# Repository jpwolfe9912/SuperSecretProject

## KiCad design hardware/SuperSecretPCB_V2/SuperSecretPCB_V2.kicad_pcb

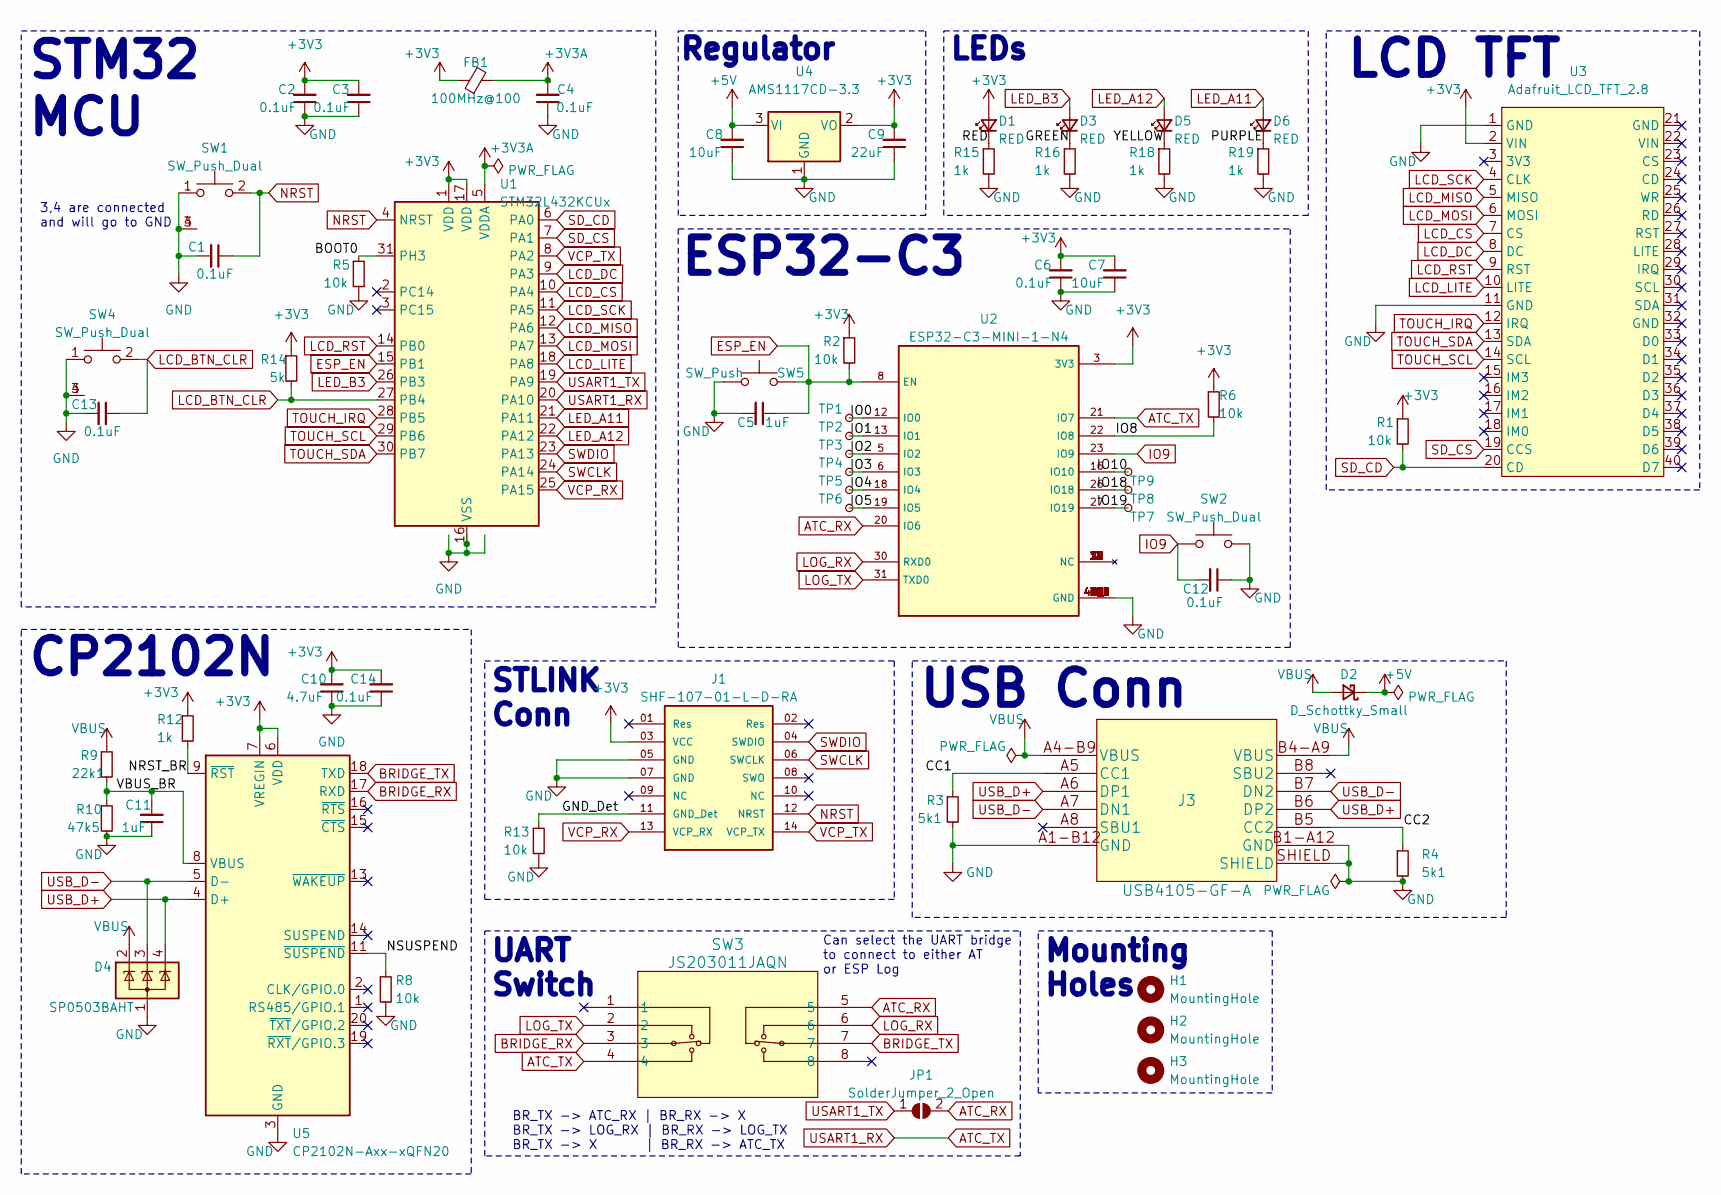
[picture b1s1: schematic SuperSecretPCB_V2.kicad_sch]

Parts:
C1, C2, C3, C4, C6, C12, C13, C14: 0.1uF; C_0603_1608Metric
C5, C11: 1uF; C_0603_1608Metric
C7, C8: 10uF; C_0603_1608Metric
C9: 22uF; C_0603_1608Metric
C10: 4.7uF; C_0603_1608Metric
D1, D3, D5, D6: RED; LED_D5.0mm_Horizontal_O1.27mm_Z3.0mm
D2: D_Schottky_Small; D_0603_1608Metric
D4: SP0503BAHT; SOT-143
FB1: 100MHz@100; C_0603_1608Metric
H1, H2, H3: MountingHole; MountingHole_2.2mm_M2
J1: SHF-107-01-L-D-RA; SAMTEC_SHF-107-01-L-D-RA
J3: USB4105-GF-A; GCT_USB4105-GF-A
JP1: SolderJumper_2_Open; PinHeader_1x02_P2.54mm_Vertical
R1, R2, R5, R6, R8, R13: 10k; R_0603_1608Metric
R3, R4: 5k1; R_0603_1608Metric
R9: 22k1; R_0603_1608Metric
R10: 47k5; R_0603_1608Metric
R12, R15, R16, R18, R19: 1k; R_0603_1608Metric
R14: 5k; R_0603_1608Metric
SW1, SW4: SW_Push_Dual; Switch_1825027-5
SW2: SW_Push_Dual; SW_SPST_B3U-1000P
SW3: JS203011JAQN; SW8_JS203011JAQN_CNK
SW5: SW_Push; SW_SPST_B3U-1000P
TP1, TP2, TP3, TP4, TP5, TP6, TP7, TP8, TP9: TP; TestPoint_Pad_D1.0mm
U1: STM32L432KCUx; QFN-32-1EP_5x5mm_P0.5mm_EP3.45x3.45mm
U2: ESP32-C3-MINI-1-N4; XCVR_ESP32-C3-MINI-1-N4; PARTREV v1.0
U3: Adafruit_LCD_TFT_2.8
U4: AMS1117CD-3.3; TO-252-2
U5: CP2102N-Axx-xQFN20; SiliconLabs_QFN-20-1EP_3x3mm_P0.5mm_EP1.8x1.8mm

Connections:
+3V3: C2.2, C3.2, C6.2, C7.2, C9.2, C10.2, C14.2, D1.2 (A), FB1.1, J1.03 (VCC), R1.1, R2.1, R6.1, R12.1, R14.1, U1.1 (VDD), U1.17 (VDD), U2.3 (3V3), U3.2 (VIN), U4.2 (VO), U5.6 (VDD), U5.7 (VREGIN)
+3V3A: C4.2, FB1.2, U1.5 (VDDA)
+5V: C8.2, D2.1 (K), U4.3 (VI)
/BOOT0: R5.1, U1.31 (PH3)
/CC1: J3.A5 (CC1), R3.1
/CC2: J3.B5 (CC2), R4.1
/GND_Det: J1.11 (GND_Det), R13.1
/GREEN: D3.1 (K), R16.1
/IO0: TP1.1, U2.12 (IO0)
/IO1: TP2.1, U2.13 (IO1)
/IO2: TP3.1, U2.5 (IO2)
/IO3: TP4.1, U2.6 (IO3)
/IO4: TP5.1, U2.18 (IO4)
/IO5: TP6.1, U2.19 (IO5)
/IO8: R6.2, U2.22 (IO8)
/IO10: TP9.1, U2.16 (IO10)
/IO18: TP8.1, U2.26 (IO18)
/IO19: TP7.1, U2.27 (IO19)
/NRST_BR: R12.2, U5.9 (~RST)
/NSUSPEND: R8.1, U5.11 (~SUSPEND)
/PURPLE: D6.1 (K), R19.1
/RED: D1.1 (K), R15.1
/VBUS_BR: C11.2, R9.2, R10.1, U5.8 (VBUS)
/YELLOW: D5.1 (K), R18.1
ATC_RX: JP1.2 (B), SW3.5, U2.20 (IO6)
ATC_TX: SW3.4, U1.20 (PA10), U2.21 (IO7)
BRIDGE_RX: SW3.3, U5.17 (RXD)
BRIDGE_TX: SW3.7, U5.18 (TXD)
ESP_EN: C5.1, R2.2, SW5.2, U1.15 (PB1), U2.8 (EN)
GND: C1.2, C2.1, C3.1, C4.1, C5.2, C6.1, C7.1, C8.1, C9.1, C10.1, C11.1, C12.1, C13.2, C14.1, D4.1 (A), J1.05 (GND), J1.07 (GND), J3.A1-B12 (GND), J3.B1-A12 (GND), J3.SHIELD, R3.2, R4.2, R5.2, R8.2, R10.2, R13.2, R15.2, R16.2, R18.2, R19.2, SW1.1, SW1.3, SW1.4, SW2.2, SW4.1, SW4.3, SW4.4, SW5.1, U1.16 (VSS), U1.32 (VSS), U1.33 (VSS), U2.1 (GND), U2.2 (GND), U2.11 (GND), U2.14 (GND), U2.36 (GND), U2.37 (GND), U2.38 (GND), U2.39 (GND), U2.40 (GND), U2.41 (GND), U2.42 (GND), U2.43 (GND), U2.44 (GND), U2.45 (GND), U2.46 (GND), U2.47 (GND), U2.48 (GND), U2.49_1 (GND), U2.49_2 (GND), U2.49_3 (GND), U2.49_4 (GND), U2.49_5 (GND), U2.49_6 (GND), U2.49_7 (GND), U2.49_8 (GND), U2.49_9 (GND), U2.50 (GND), U2.51 (GND), U2.52 (GND), U2.53 (GND), U3.1 (GND), U3.11 (GND), U4.1 (GND), U5.3 (GND), U5.12 (GND), U5.21 (GND)
IO9: C12.2, SW2.1, U2.23 (IO9)
LCD_BTN_CLR: C13.1, R14.2, SW4.2, U1.27 (PB4)
LCD_CS: U1.10 (PA4), U3.7 (CS)
LCD_DC: U1.9 (PA3), U3.8 (DC)
LCD_LITE: U1.18 (PA8), U3.10 (LITE)
LCD_MISO: U1.12 (PA6), U3.5 (MISO)
LCD_MOSI: U1.13 (PA7), U3.6 (MOSI)
LCD_RST: U1.14 (PB0), U3.9 (RST)
LCD_SCK: U1.11 (PA5), U3.4 (CLK)
LED_A11: D6.2 (A), U1.21 (PA11)
LED_A12: D5.2 (A), U1.22 (PA12)
LED_B3: D3.2 (A), U1.26 (PB3)
LOG_RX: SW3.6, U2.30 (RXD0)
LOG_TX: SW3.2, U2.31 (TXD0)
NRST: C1.1, J1.12 (NRST), SW1.2, U1.4 (NRST)
SD_CD: R1.2, U1.6 (PA0), U3.20 (CD)
SD_CS: U1.7 (PA1), U3.19 (CCS)
SWCLK: J1.06 (SWCLK), U1.24 (PA14)
SWDIO: J1.04 (SWDIO), U1.23 (PA13)
TOUCH_IRQ: U1.28 (PB5), U3.12 (IRQ)
TOUCH_SCL: U1.29 (PB6), U3.14 (SCL)
TOUCH_SDA: U1.30 (PB7), U3.13 (SDA)
USART1_TX: JP1.1 (A), U1.19 (PA9)
USB_D+: D4.4 (K), J3.A6 (DP1), J3.B6 (DP2), U5.4 (D+)
USB_D-: D4.3 (K), J3.A7 (DN1), J3.B7 (DN2), U5.5 (D-)
VBUS: D2.2 (A), D4.2 (K), J3.A4-B9 (VBUS), J3.B4-A9 (VBUS), R9.1
VCP_RX: J1.13 (VCP_RX), U1.25 (PA15)
VCP_TX: J1.14 (VCP_TX), U1.8 (PA2)

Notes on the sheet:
STLINK Conn
LEDs
UART Switch
STM32 MCU
BR_TX -> ATC_RX | BR_RX -> X BR_TX -> LOG_RX | BR_RX -> LOG_TX BR_TX -> X | BR_RX -> ATC_TX
CP2102N
Regulator
ESP32-C3
LCD TFT
Can select the UART bridge to connect to either AT or ESP Log
Mounting Holes
USB Conn
3,4 are connected and will go to GND

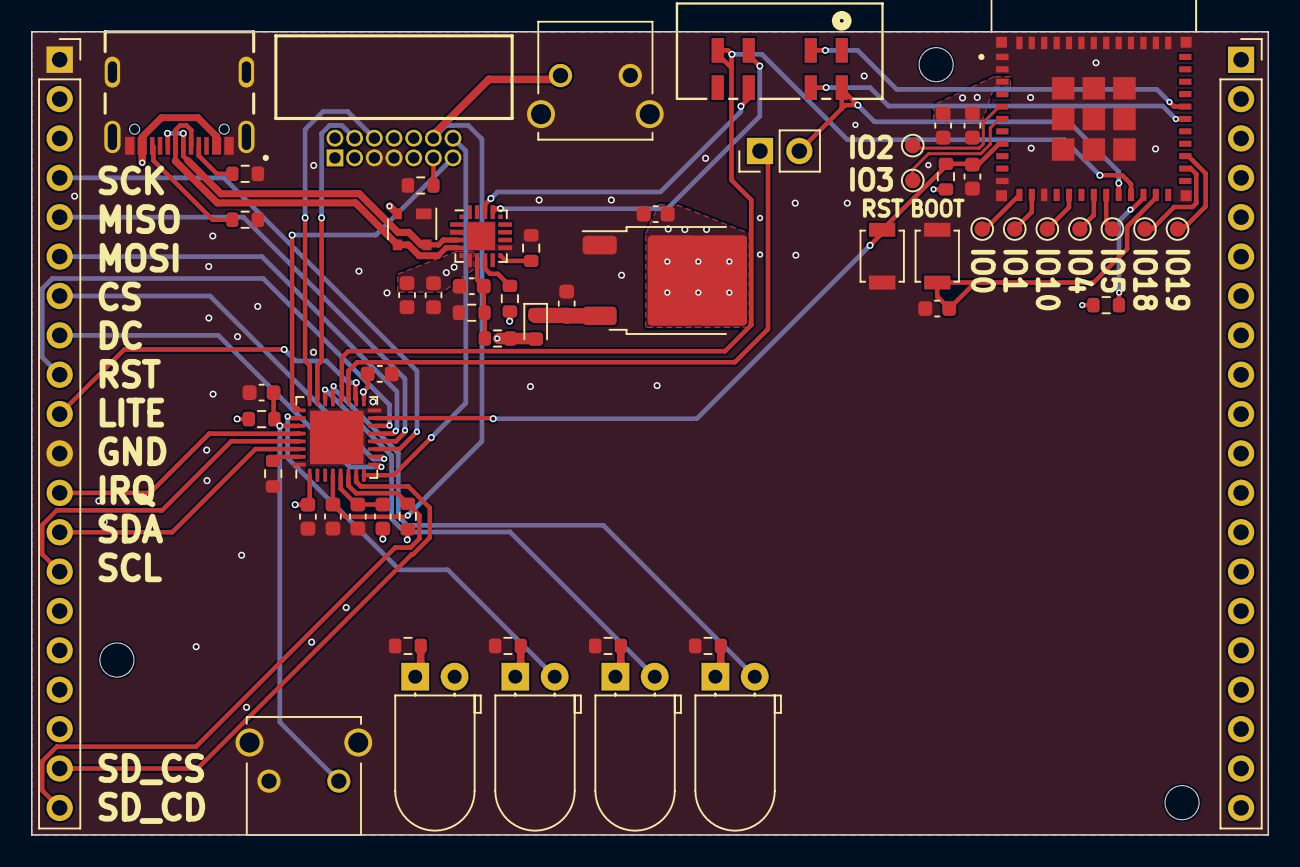
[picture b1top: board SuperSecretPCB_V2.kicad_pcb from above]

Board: 4 copper layers, 79.8 x 51.8 mm, 62 parts (0 on the bottom side), 58 nets.

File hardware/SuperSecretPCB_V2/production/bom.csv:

Designator,Footprint,Quantity,Value,LCSC Part #
"C1, C12, C13, C14, C2, C3, C4, C6",0603,8,0.1uF,
C10,0603,1,4.7uF,
"C11, C5",0603,2,1uF,
"C7, C8",0603,2,10uF,
C9,0603,1,22uF,
"D1, D3, D5, D6",LED_D5.0mm_Horizontal_O1.27mm_Z3.0mm,4,RED,
D2,0603,1,D_Schottky_Small,
D4,SOT-143,1,SP0503BAHT,
FB1,0603,1,100MHz@100,
"H1, H2, H3",MountingHole_2.2mm_M2,3,MountingHole,
J1,SAMTEC_SHF-107-01-L-D-RA,1,SHF-107-01-L-D-RA,
J3,GCT_USB4105-GF-A,1,USB4105-GF-A,
JP1,PinHeader_1x02_P2.54mm_Vertical,1,SolderJumper_2_Open,
"R1, R13, R2, R5, R6, R8",0603,6,10k,
R10,0603,1,47k5,
"R12, R15, R16, R18, R19",0603,5,1k,
R14,0603,1,5k,
"R3, R4",0603,2,5k1,
R9,0603,1,22k1,
"SW1, SW4",Switch_1825027-5,2,SW_Push_Dual,
SW2,SW_SPST_B3U-1000P,1,SW_Push_Dual,
SW3,SW8_JS203011JAQN_CNK,1,JS203011JAQN,
SW5,SW_SPST_B3U-1000P,1,SW_Push,
"TP1, TP2, TP3, TP4, TP5, TP6, TP7, TP8, TP9",TestPoint_Pad_D1.0mm,9,TP,
U1,QFN-32-1EP_5x5mm_P0.5mm_EP3.45x3.45mm,1,STM32L432KCUx,
U2,XCVR_ESP32-C3-MINI-1-N4,1,ESP32-C3-MINI-1-N4,
U3,Adafruit_LCD_TFT_2.8,1,Adafruit_LCD_TFT_2.8,
U4,TO-252-2,1,AMS1117CD-3.3,
U5,SiliconLabs_QFN-20-1EP_3x3mm_P0.5mm_EP1.8x1.8mm,1,CP2102N-Axx-xQFN20,

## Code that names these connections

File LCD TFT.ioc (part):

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Mcu.Name=STM32L432K(B-C)Ux
Mcu.Package=UFQFPN32
Mcu.UserName=STM32L432KCUx
PA10.Mode=Asynchronous
PA10.Signal=USART1_RX
PA13\ (JTMS-SWDIO).Mode=Serial_Wire
PA13\ (JTMS-SWDIO).Signal=SYS_JTMS-SWDIO
PA14\ (JTCK-SWCLK).Mode=Serial_Wire
PA14\ (JTCK-SWCLK).Signal=SYS_JTCK-SWCLK
PA3.GPIOParameters=GPIO_Label
PA3.GPIO_Label=D_C
PA3.Signal=GPIO_Output
PA4.GPIOParameters=GPIO_Label
PA4.GPIO_Label=SPI1_CS
PA4.Signal=GPIO_Output
PA5.Mode=Full_Duplex_Master
PA5.Signal=SPI1_SCK
PA6.Mode=Full_Duplex_Master
PA6.Signal=SPI1_MISO
PA7.Mode=Full_Duplex_Master
PA7.Signal=SPI1_MOSI
PA9.Mode=Asynchronous
PA9.Signal=USART1_TX
PB6.Mode=I2C
PB6.Signal=I2C1_SCL
PB7.Mode=I2C
PB7.Signal=I2C1_SDA
RCC.HSE_VALUE=8000000
RCC.SYSCLKFreq_VALUE=80000000
RCC.SYSCLKSource=RCC_SYSCLKSOURCE_PLLCLK
board=custom

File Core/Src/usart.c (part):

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
    LL_AHB2_GRP1_EnableClock(LL_AHB2_GRP1_PERIPH_GPIOA);
    /**USART1 GPIO Configuration
    PA9   ------> USART1_TX
    PA10   ------> USART1_RX
    */
    GPIO_InitStruct.Pin = LL_GPIO_PIN_9 | LL_GPIO_PIN_10;
    GPIO_InitStruct.Mode = LL_GPIO_MODE_ALTERNATE;
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
    LL_AHB2_GRP1_EnableClock(LL_AHB2_GRP1_PERIPH_GPIOA);
    /**USART2 GPIO Configuration
    PA2   ------> USART2_TX
    PA15 (JTDI)   ------> USART2_RX
    */
    GPIO_InitStruct.Pin = LL_GPIO_PIN_2;
    GPIO_InitStruct.Mode = LL_GPIO_MODE_ALTERNATE;
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
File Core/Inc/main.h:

/**
 * @file    main.h
 * @brief   Header for main.c file.
 *              This file contains the common defines of the application.
 */

#ifndef __MAIN_H__
#define __MAIN_H__

#ifdef __cplusplus
extern "C"
{
#endif

/* Includes */
#include "super_secret_project.h"

/* Defines */
#define USE_LCD
#define USE_TOUCH

/* Functions Prototypes */
void Error_Handler(void);

/* Defines */
#define DC_Pin LL_GPIO_PIN_3
#define DC_GPIO_Port GPIOA
#define LCD_CS_Pin LL_GPIO_PIN_4
#define LCD_CS_GPIO_Port GPIOA

#define LCD_RST_Pin LL_GPIO_PIN_1
#define LCD_RST_Port GPIOB
#define LED_Pin LL_GPIO_PIN_3
#define LED_GPIO_Port GPIOB
#define BTN_Pin LL_GPIO_PIN_4
#define BTN_GPIO_Port GPIOB
#define TOUCH_IRQ_Pin LL_GPIO_PIN_5
#define TOUCH_IRQ_GPIO_Port GPIOB

#define SEND_RATE frame1Hz
#define READ_RATE frame1000Hz
#define DRAW_RATE frame10Hz

#ifdef __cplusplus
}
#endif

#endif /* __MAIN_H__ */

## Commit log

2023-03-16 Cleaned up and refactored a lot of code
2023-03-31 Reduced code to functions.Added macros for LCD use
2023-03-31 Includes main.h
2023-03-31 Include fatfs config
2023-03-31 Adding changees
2023-03-31 .gitignore is now working
2023-03-31 Added gitignore
2023-04-01 Cleaned up code and added unbrick function
2023-04-01 Cleaned up function
2023-04-01 Made more robust by checking data values
2023-04-01 Added constrain and cleaned up other functions
2023-04-01 Changed rx to circular
2023-04-01 No real changes. Considered changing priorities
2023-04-01 Added timeout to read function
2023-04-01 Changed read variable
2023-04-01 Changed rx to no mem inc so it doesn't overwrite
2023-04-01 Updated gitignore
2023-04-01 Removed unused libraries
2023-04-02 Added doxygen comments
2023-04-03 Changed coordinate rb size
2023-04-03 Include leds.h
2023-04-03 Include graphics.h
2023-04-03 Increased uart rx rb tp 2048 bytes
2023-04-03 Removed unused code
2023-04-03 Fixed memory usage errors in listen function
2023-04-03 Cleaned up function call names
2023-04-03 Removed unused functions
2023-04-03 Cleaned up a little
2023-04-04 Changed coordinate rb size back to 100
2023-04-04 Added macros for other frame rates
2023-04-04 Cleaned up how coordinates are read and drawn
2023-04-04 Added lcd reset function to clear screen
2023-04-10 changed coord size macro to 200
2023-04-10 Changed listen function to not need a search idx
2023-04-10 Added coords available tracker
2023-04-10 Cleaned up unused code
2023-04-10 Removed usart_rx_check in dma handler
2023-04-13 Added PCB files and rearranged
2023-04-13 Added 3D PNGs
2023-05-01 Deleted backups and added documentation
2023-06-11 Removed unused funciton prototype
2023-06-11 Added device ID to Wifi struct
2023-06-11 Added function for finding device ID
2023-06-11 Fixed reset recursive loop
2023-07-21 Delete SuperSecretPCB_V2.pdf
    Removed PDF
2023-07-21 Readded PDF

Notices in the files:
parts and their libraries:
Copyright 2021 Accelerated Designs. All rights reserved.
